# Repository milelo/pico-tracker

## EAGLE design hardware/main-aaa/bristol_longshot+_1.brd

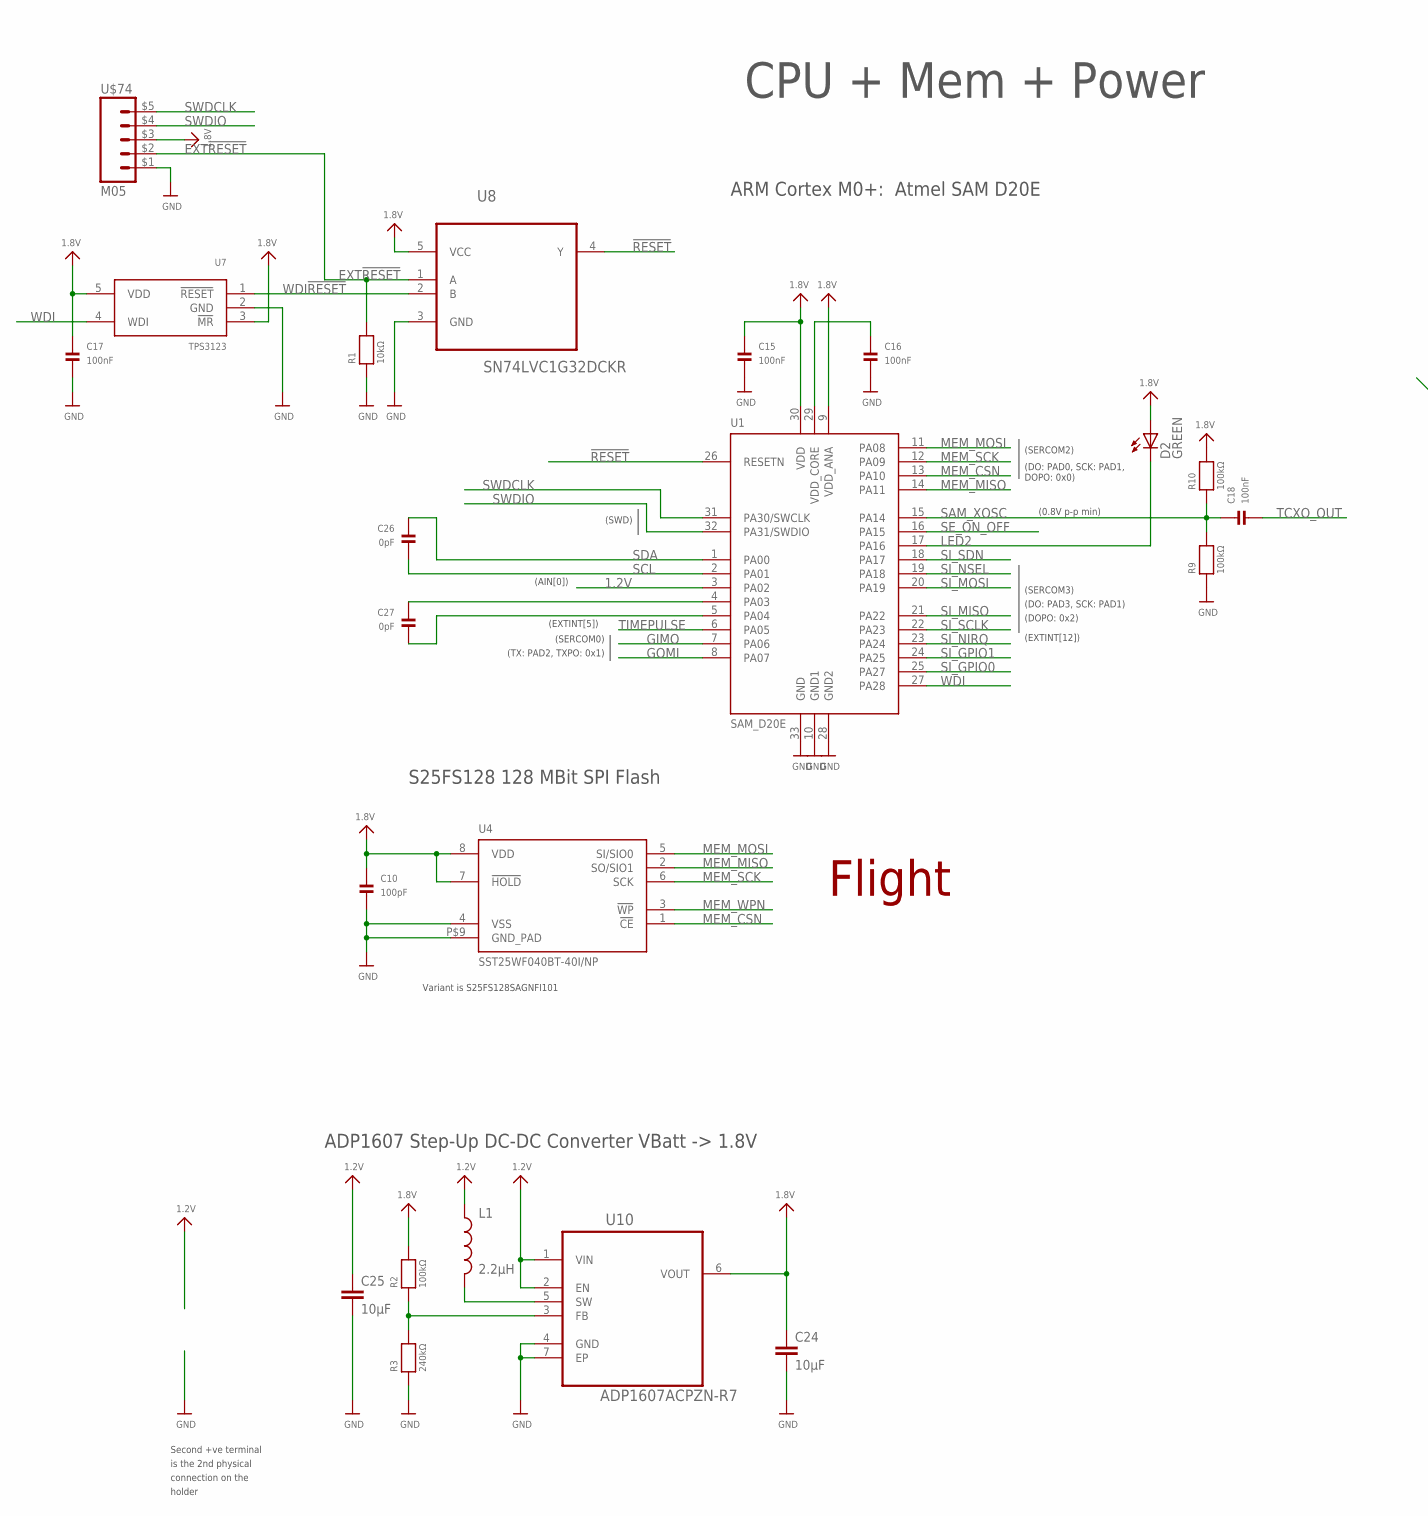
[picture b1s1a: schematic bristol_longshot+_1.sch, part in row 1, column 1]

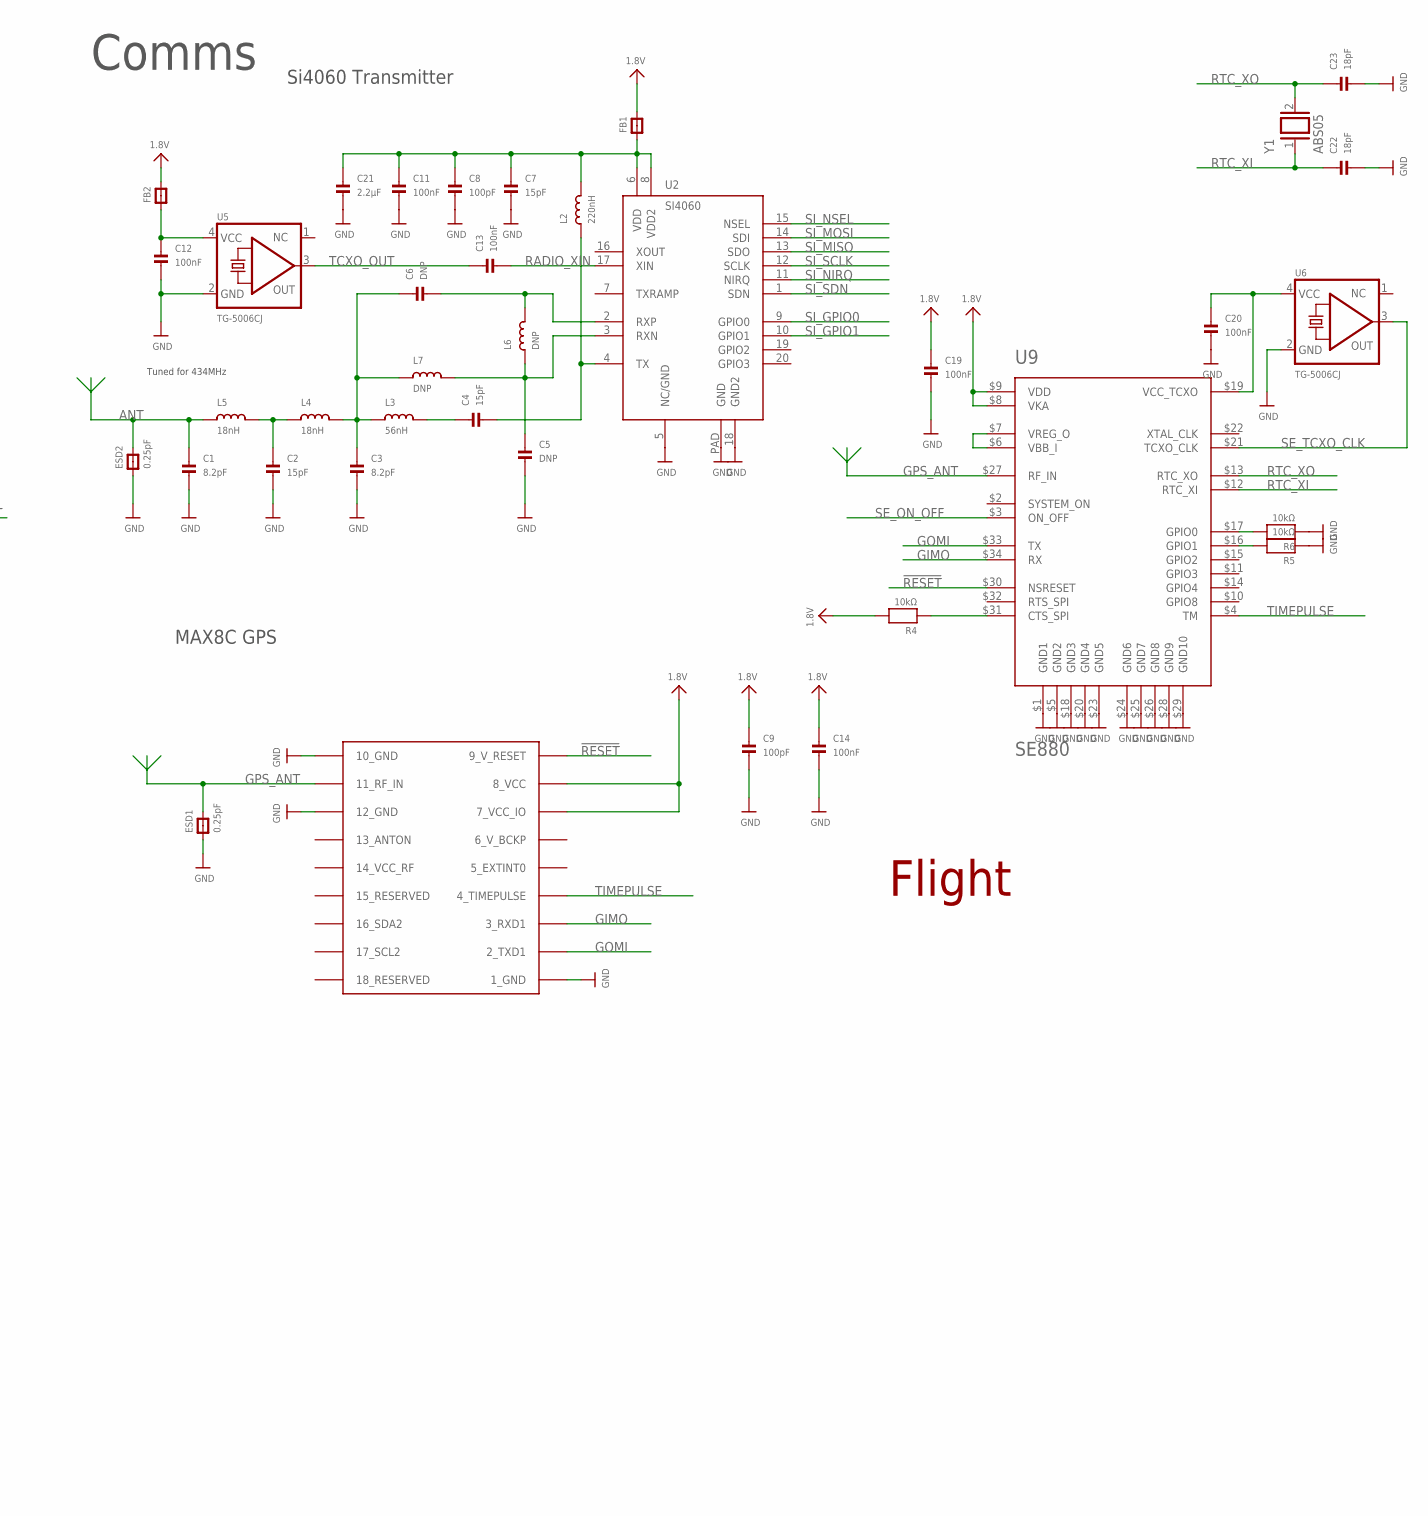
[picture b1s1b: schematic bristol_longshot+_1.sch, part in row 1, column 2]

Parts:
C1, C3: 8.2pF; _0402
C2, C4, C7: 15pF; _0402
C5, C6: DNP; _0402
C8, C9, C10: 100pF; _0402
C11, C12, C13, C14, C15, C16, C17, C18, C19, C20: 100nF; _0402
C21: 2.2µF; _0402
C22, C23: 18pF; _0402
C24, C25: 10µF; C0603K
C26, C27: 0pF; _0402
D2: GREEN; CHIPLED_0603
ESD1, ESD2: 0.25pF; _0603MP
FB1, FB2: FERRITE_0402; _0402
L1: 2.2µH; 1007
L2: 220nH; _0402
L3: 56nH; _0402
L4, L5: 18nH; _0402
L6, L7: DNP; _0402
R1, R4, R5, R6: 10kΩ; _0402
R2, R9, R10: 100kΩ; _0402
R3: 240kΩ; _0402
U1: SAM_D20E; QFN32_5MM
U2: SI4060; QFN20
U3: UBLOX_MAX
U4: SST25WF040BT-40I/NP; USON-8
U5, U6: TG-5006CJ; TC-5006CJ
U7: TPS3123; SOT23-5
U8: SN74LVC1G32DCKR; SOT65P210X110-5N
U9: SE880
U10: ADP1607ACPZN-R7; DFN200X200X60-7N
U$74: M05; M05_SIDE
Y1: ABS05

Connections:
1.2V: C25.1, L1.1, U1.3 (PA02), U10.1 (VIN), U10.2 (EN)
1.8V: C9.1, C10.1, C14.1, C15.1, C17.1, C19.1, C24.1, D2.A, FB1.2, FB2.2, R2.2, R4.2, R10.2, U1.9 (VDD_ANA), U1.30 (VDD), U3.7_VCC_IO, U3.8_VCC, U4.7 (!HOLD), U4.8 (VDD), U7.3 (!MR), U7.5 (VDD), U8.5 (VCC), U9.$8 (VKA), U9.$9 (VDD), U10.6 (VOUT), U$74.$3 (3)
!RESET: U1.26 (RESETN), U3.9_V_RESET, U8.4 (Y), U9.$30 (NSRESET)
ANT: C1.1, ESD2.2, L5.1
EXT!RESET: R1.2, U8.1 (A), U$74.$2 (2)
FB: R2.1, R3.2, U10.3 (FB)
FILTER1: C3.1, C6.1, L3.1, L4.2, L7.1
FILTER2: C2.1, L4.1, L5.2
GIMO: U1.7 (PA06), U3.3_RXD1, U9.$34 (RX)
GND: C1.2, C2.2, C3.2, C5.2, C7.2, C8.2, C9.2, C10.2, C11.2, C12.2, C14.2, C15.2, C16.2, C17.2, C19.2, C20.2, C21.2, C22.2, C23.2, C24.2, C25.2, ESD1.1, ESD2.1, R1.1, R3.1, R5.1, R6.1, R9.1, U1.10 (GND1), U1.28 (GND2), U1.33 (GND), U2.5 (NC/GND), U2.18 (GND2), U2.PAD (GND), U3.1_GND, U3.10_GND, U3.12_GND, U4.4 (VSS), U4.P$9 (GND_PAD), U5.2 (GND), U6.2 (GND), U7.2 (GND), U8.3 (GND), U9.$1 (GND1), U9.$5 (GND2), U9.$18 (GND3), U9.$20 (GND4), U9.$23 (GND5), U9.$24 (GND6), U9.$25 (GND7), U9.$26 (GND8), U9.$28 (GND9), U9.$29 (GND10), U10.4 (GND), U10.7 (EP), U$74.$1 (1)
GOMI: U1.8 (PA07), U3.2_TXD1, U9.$33 (TX)
GPS_ANT: ESD1.2, U3.11_RF_IN, U9.$27 (RF_IN)
LED2: D2.C, U1.17 (PA16)
MEM_CSN: U1.13 (PA10), U4.1 (!CE)
MEM_MISO: U1.14 (PA11), U4.2 (SO/SIO1)
MEM_MOSI: U1.11 (PA08), U4.5 (SI/SIO0)
MEM_SCK: U1.12 (PA09), U4.6 (SCK)
MEM_WPN: U4.3 (!WP)
unnamed: C27.1, U1.4 (PA03)
unnamed: R6.2, U9.$17 (GPIO0)
unnamed: C27.2, U1.5 (PA04)
unnamed: R5.2, U9.$16 (GPIO1)
RADIO_VDD: C7.1, C8.1, C11.1, C21.1, FB1.1, L2.2, U2.6 (VDD), U2.8 (VDD2)
RADIO_XIN: C13.2, U2.17 (XIN)
RF_OUT: C4.2, L2.1, U2.4 (TX)
RF_TANK: C4.1, L3.2
RTC_XI: C22.1, U9.$12 (RTC_XI), Y1.1
RTC_XO: C23.1, U9.$13 (RTC_XO), Y1.2
RXN: C5.1, L6.1, L7.2, U2.3 (RXN)
RXP: C6.2, L6.2, U2.2 (RXP)
SAM_XOSC: C18.1, R9.2, R10.1, U1.15 (PA14)
SCL: C26.2, U1.2 (PA01)
SDA: C26.1, U1.1 (PA00)
SE_MODE_PULL: R4.1, U9.$31 (CTS_SPI)
SE_ON_OFF: U1.16 (PA15), U9.$3 (ON_OFF)
SE_TCXO_CLK: U6.3 (OUT), U9.$21 (TCXO_CLK)
SE_VCO_TCXO: C20.1, U6.4 (VCC), U9.$19 (VCC_TCXO)
SE_VREG: U9.$6 (VBB_I), U9.$7 (VREG_O)
SI_GPIO0: U1.25 (PA27), U2.9 (GPIO0)
SI_GPIO1: U1.24 (PA25), U2.10 (GPIO1)
SI_MISO: U1.21 (PA22), U2.13 (SDO)
SI_MOSI: U1.20 (PA19), U2.14 (SDI)
SI_NIRQ: U1.23 (PA24), U2.11 (NIRQ)
SI_NSEL: U1.19 (PA18), U2.15 (NSEL)
SI_SCLK: U1.22 (PA23), U2.12 (SCLK)
SI_SDN: U1.18 (PA17), U2.1 (SDN)
SW: L1.2, U10.5 (SW)
SWDCLK: U1.31 (PA30/SWCLK), U$74.$5 (5)
SWDIO: U1.32 (PA31/SWDIO), U$74.$4 (4)
TCXO_OUT: C13.1, C18.2, U5.3 (OUT)
TCXO_VDD: C12.1, FB2.1, U5.4 (VCC)
TIMEPULSE: U1.6 (PA05), U3.4_TIMEPULSE, U9.$4 (TM)
VDD_CORE: C16.1, U1.29 (VDD_CORE)
WDI: U1.27 (PA28), U7.4 (WDI)
WDI!RESET: U7.1 (!RESET), U8.2 (B)

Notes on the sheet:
ARM Cortex M0+: Atmel SAM D20E
(SERCOM3)
(SWD)
(EXTINT[12])
(DO: PAD3, SCK: PAD1)
(DOPO: 0x2)
(SERCOM2)
(DO: PAD0, SCK: PAD1, DOPO: 0x0)
(SERCOM0)
(TX: PAD2, TXPO: 0x1)
S25FS128 128 MBit SPI Flash
Variant is S25FS128SAGNFI101
MAX8C GPS
Si4060 Transmitter
Tuned for 434MHz
CPU + Mem + Power
Comms
Flight
(EXTINT[5])
(0.8V p-p min)
(AIN[0])
ADP1607 Step-Up DC-DC Converter VBatt -> 1.8V
Second +ve terminal is the 2nd physical connection on the holder

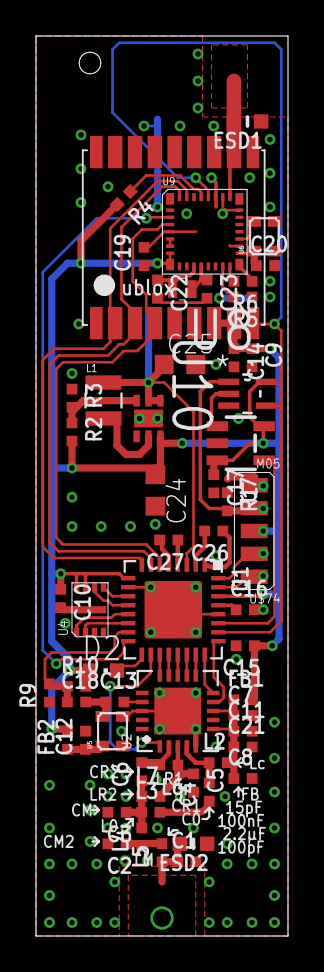
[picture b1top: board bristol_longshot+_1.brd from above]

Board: 2 copper layers, 14.0 x 50.0 mm, 59 parts (0 on the bottom side), 54 nets.

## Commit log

2016-06-21 Added revised boards and BOM in csv
2016-07-14 Interim eclipse configuration

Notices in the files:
parts and their libraries:
microbuilder_v3: This work is placed in the public domain, and may be freely used for commercial and non-commercial work with the following conditions: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
SparkFun: Licensing: CC v3.0 Share-Alike You are welcome to use this library for commercial purposes.
